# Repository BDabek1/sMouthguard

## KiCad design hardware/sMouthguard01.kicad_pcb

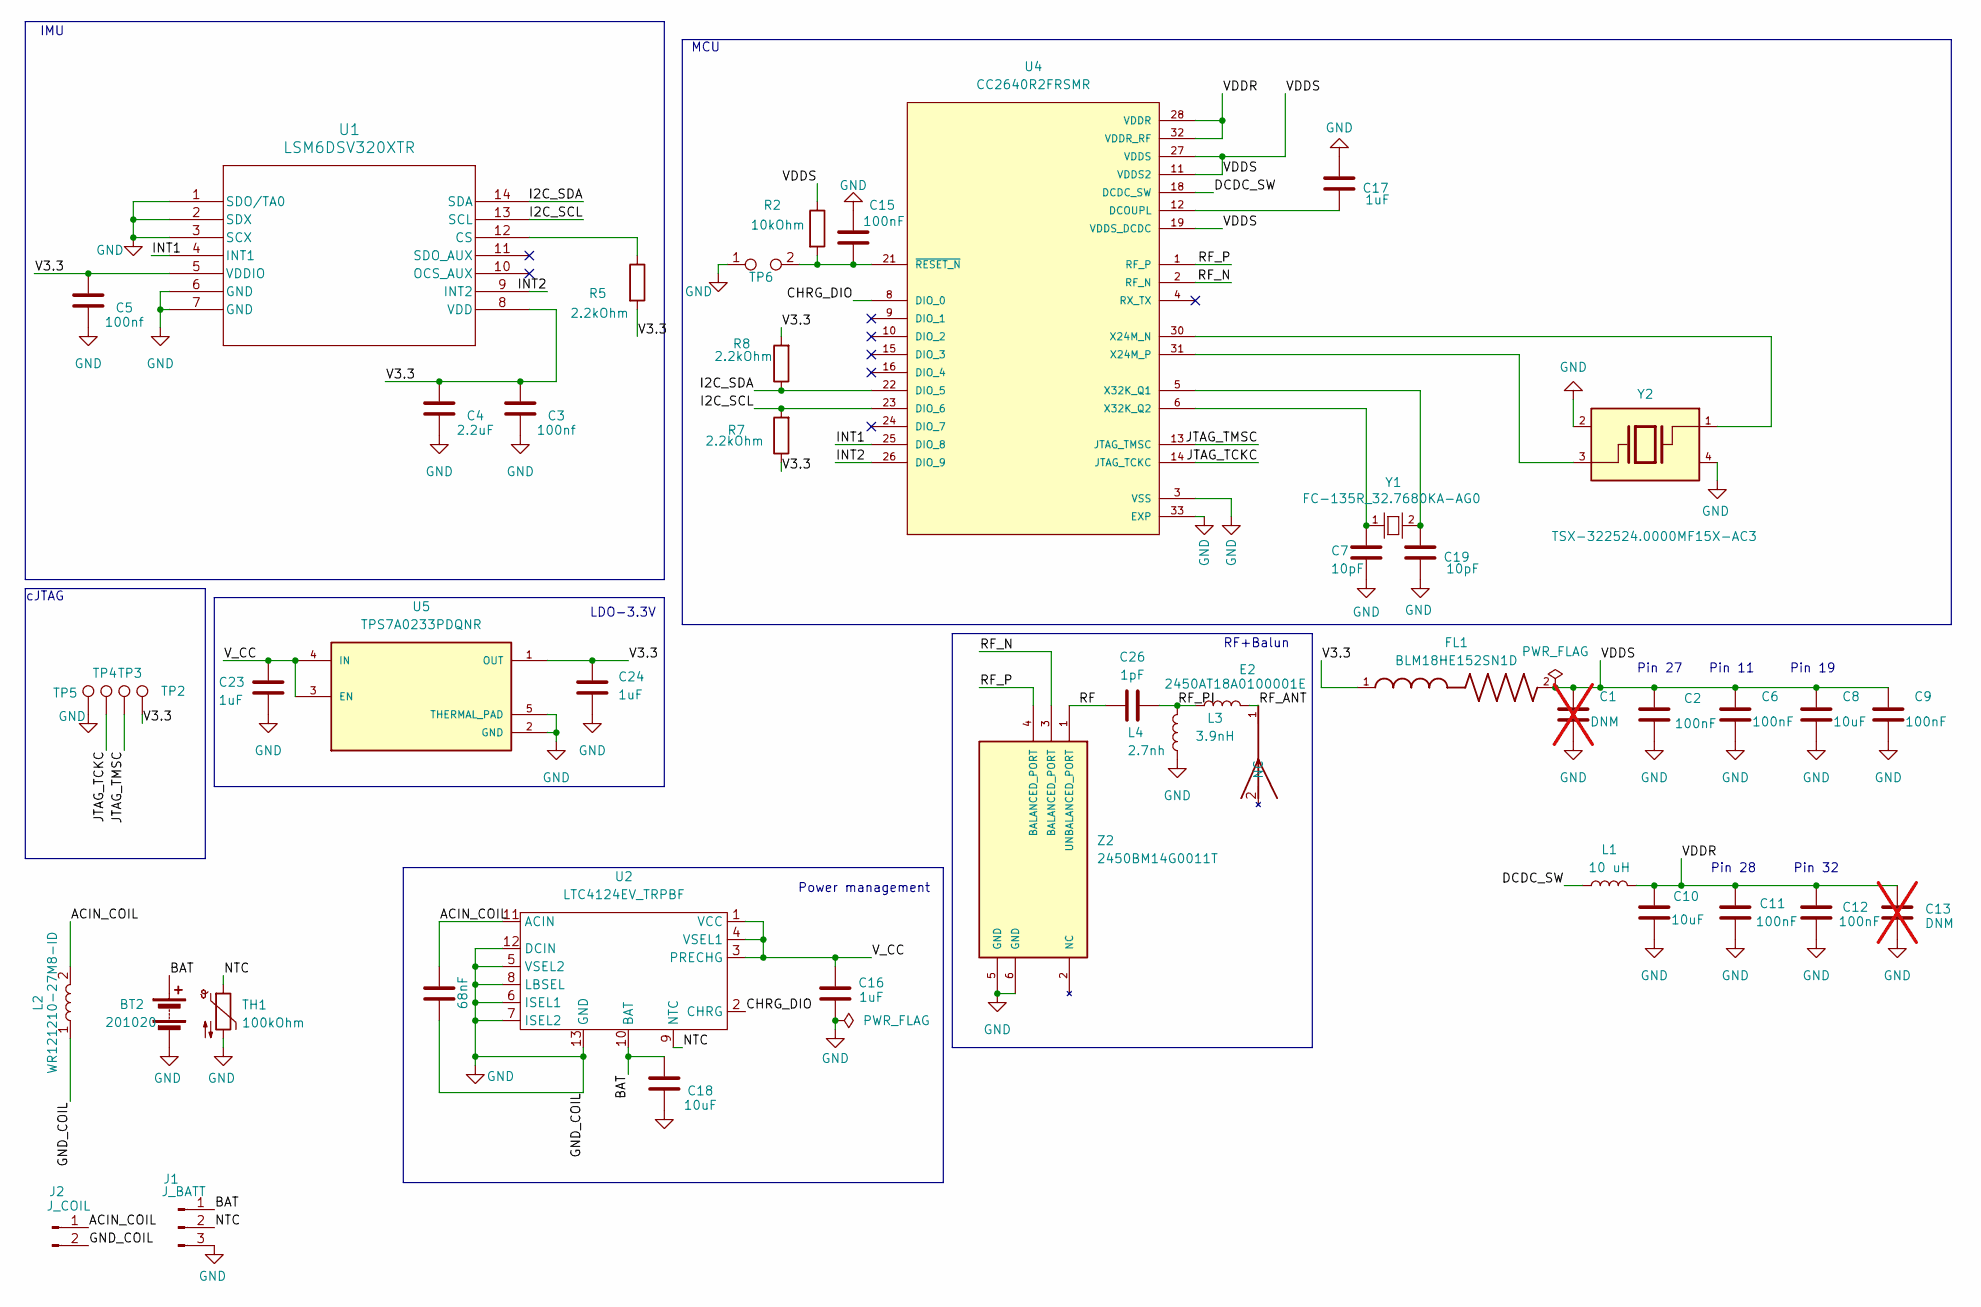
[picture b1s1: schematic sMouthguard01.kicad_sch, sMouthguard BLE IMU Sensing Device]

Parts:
BT2: 201020
C1, C13: DNM; C_0201_0603Metric; not fitted
C2, C6, C9, C11, C12, C15: 100nF; C_0201_0603Metric
C3, C5: 100nf; C_0201_0603Metric
C4: 2.2uF; C_0402_1005Metric
C7, C19: 10pF; C_0201_0603Metric
C8, C10, C18: 10uF; C_0201_0603Metric
C14: 68nF; C_0603_1608Metric
C16: 1uF; C_0402_1005Metric
C17, C23, C24: 1uF; C_0201_0603Metric
C26: 1pF; C_0402_1005Metric
E2: 2450AT18A0100001E; XCVR_2450AT18A0100001E; PARTREV 4.0
FL1: BLM18HE152SN1D; BEADC1608X95N
J1: J_BATT; SolderWire-0.1sqmm_1x03_P3.6mm_D0.4mm_OD1mm
J2: J_COIL; SolderWire-0.1sqmm_1x02_P3.6mm_D0.4mm_OD1mm
L1: 10 uH; L_0603_1608Metric
L2: WR121210-27M8-ID
L3: 3.9nH; L_0402_1005Metric
L4: 2.7nh; L_0402_1005Metric
R2: 10kOhm; R_0402_1005Metric
R5, R7, R8: 2.2kOhm; R_0402_1005Metric
TH1: 100kOhm; R_0402_1005Metric
TP2: 3.3V; TestPoint_Pad_D1.0mm
TP3: JTAG_TMSC; TestPoint_Pad_D1.0mm
TP4: JTAG_TCKC; TestPoint_Pad_D1.0mm
TP5: GND; TestPoint_Pad_D1.0mm
TP6: TP; SolderJumper-2_P1.3mm_Open_Pad1.0x1.5mm
U1: LSM6DSV320XTR; LGA-14L_2p5X3X0p83_STM
U2: LTC4124EV_TRPBF; QFN50P200X200X83-13N
U4: CC2640R2FRSMR; QFN40P400X400X100-33N
U5: TPS7A0233PDQNR; IC_TPS7A0233PDQNR; PARTREV C
Y1: FC-135R_32.7680KA-AG0; Crystal_SMD_3215-2Pin_3.2x1.5mm
Y2: TSX-322524.0000MF15X-AC3; OSCCC320X250X60; PARTREV N/A
Z2: 2450BM14G0011T; BALUN_2450BM14G0011T; PARTREV 2.0

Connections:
/ACIN_COIL: C14.1, J2.1, L2.2, U2.11 (ACIN)
/BAT: BT2.1 (+), C18.1, J1.1, U2.10 (BAT)
/CHRG_DIO: U2.2 (CHRG), U4.8 (DIO_0)
/DCDC_SW: L1.1, U4.18 (DCDC_SW)
/I2C_SCL: R7.2, U1.13 (SCL), U4.23 (DIO_6)
/I2C_SDA: R8.1, U1.14 (SDA), U4.22 (DIO_5)
/INT1: U1.4 (INT1), U4.25 (DIO_8)
/INT2: U1.9 (INT2), U4.26 (DIO_9)
/JTAG_TCKC: TP4.1, U4.14 (JTAG_TCKC)
/JTAG_TMSC: TP3.1, U4.13 (JTAG_TMSC)
/NTC: J1.2, TH1.1, U2.9 (NTC)
/RF: C26.1, Z2.1 (UNBALANCED_PORT)
/RF_ANT: E2.1, L3.2
/RF_N: U4.2 (RF_N), Z2.3 (BALANCED_PORT)
/RF_P: U4.1 (RF_P), Z2.4 (BALANCED_PORT)
/RF_PI: C26.2, L3.1, L4.2
/V3.3: C3.1, C4.1, C5.1, C24.2, FL1.1, R5.2, R7.1, R8.2, TP2.1, U1.5 (VDDIO), U1.8 (VDD), U5.1 (OUT)
/VDDR: C10.1, C11.1, C12.1, C13.1, L1.2, U4.28 (VDDR), U4.32 (VDDR_RF)
/VDDS: C1.1, C2.1, C6.1, C8.1, C9.1, FL1.2, R2.1, U4.11 (VDDS2), U4.19 (VDDS_DCDC), U4.27 (VDDS)
/V_CC: C16.1, C23.2, U2.1 (VCC), U2.3 (PRECHG), U2.4 (VSEL1), U5.3 (EN), U5.4 (IN)
GND: BT2.2 (-), C1.2, C2.2, C3.2, C4.2, C5.2, C6.2, C7.2, C8.2, C9.2, C10.2, C11.2, C12.2, C13.2, C14.2, C15.1, C16.2, C17.1, C18.2, C19.2, C23.1, C24.1, J1.3, J2.2, L2.1, L4.1, TH1.2, TP5.1, TP6.1, U1.1 (SDO/TA0), U1.2 (SDX), U1.3 (SCX), U1.6 (GND), U1.7 (GND), U2.5 (VSEL2), U2.6 (ISEL1), U2.7 (ISEL2), U2.8 (LBSEL), U2.12 (DCIN), U2.13 (GND), U4.3 (VSS), U4.7 (VSS), U4.17 (VSS), U4.20 (VSS), U4.29 (VSS), U4.33 (EXP), U4.33_1 (EXP), U4.33_2 (EXP), U4.33_3 (EXP), U4.33_4 (EXP), U4.33_5 (EXP), U5.2 (GND), U5.5 (THERMAL_PAD), Y2.2, Y2.4, Z2.5 (GND), Z2.6 (GND)
unnamed: R5.1, U1.12 (CS)
unnamed: C17.2, U4.12 (DCOUPL)
unnamed: U4.30 (X24M_N), Y2.1
unnamed: U4.31 (X24M_P), Y2.3
unnamed: C19.1, U4.5 (X32K_Q1), Y1.2
unnamed: C7.1, U4.6 (X32K_Q2), Y1.1
unnamed: C15.2, R2.2, TP6.2, U4.21 (~RESET_N)

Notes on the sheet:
RF+Balun
Power management
Pin 19
LDO-3.3V
IMU
Pin 32
Pin 27
Pin 28
MCU
cJTAG
Pin 11

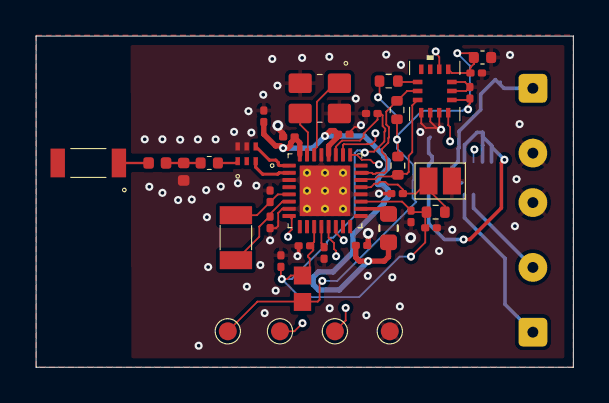
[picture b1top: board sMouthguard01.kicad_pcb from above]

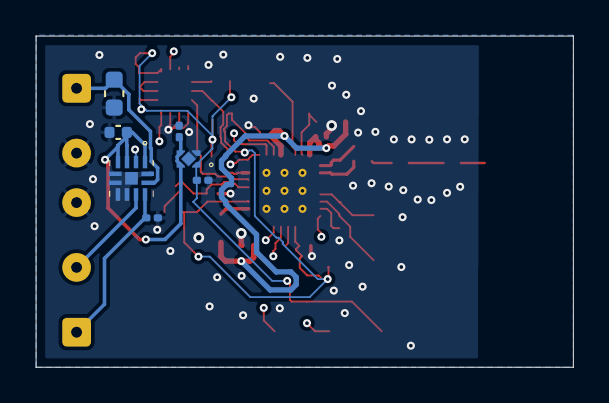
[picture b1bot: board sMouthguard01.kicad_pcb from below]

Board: 4 copper layers, 29.9 x 18.4 mm, 45 parts (9 on the bottom side), 28 nets.

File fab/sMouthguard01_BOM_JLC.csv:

Comment,Designator,Footprint,LCSC Part #
100nF 6.3V X5R,"C2,C3,C5,C6,C9,C11,C12,C15",0201,C160831
2.2uF 6.3V X5R CL03A225MQ3CRNC,"C8,C18",0201,C77762
4.7uF 6.3V X5R GRM035R60J475ME15D,"C10,C13",0201,
1uF 10V X5R,"C17,C23,C24",0201,C76935
10pF 50V C0G,"C7,C19",0201,C76921
2.2uF 6.3V X5R,C4,0402,C12530
1uF 25V X5R,C16,0402,C52923
1pF 50V C0G +/-0.1pF,C26,0402,C76898
68nF 50V X7R,C14,0603,C31658
10uH MLZ1608N100LT000,L1,0603,C194437
3.9nH LQG15HS3N9S02D,L3,0402,C77109
2.7nH LQG15HS2N7S02D,L4,0402,C77108
10k 1%,R2,0402,C25744
2.2k 1%,"R5,R7,R8",0402,C25879
BLM18HE152SN1D,FL1,0603,C82155
CC2640R2FRSMR,U4,VQFN-32_4x4mm,C133236
LTC4124EV#TRPBF,U2,LQFN-12_2x2mm,C687345
TPS7A0233PDQNR,U5,X2SON-4_1x1mm,C2860046
LSM6DSV320XTR,U1,LGA-14_2.5x3mm,
2450BM14G0011T,Z2,0603-6pad,C2917723
2450AT18A100E (=2450AT18A0100001E),E2,3216,C89334
FC-135R 32.7680KA-AG0,Y1,3215,
TSX-3225 24.0000MF15X-AC3,Y2,3225-4pad,
